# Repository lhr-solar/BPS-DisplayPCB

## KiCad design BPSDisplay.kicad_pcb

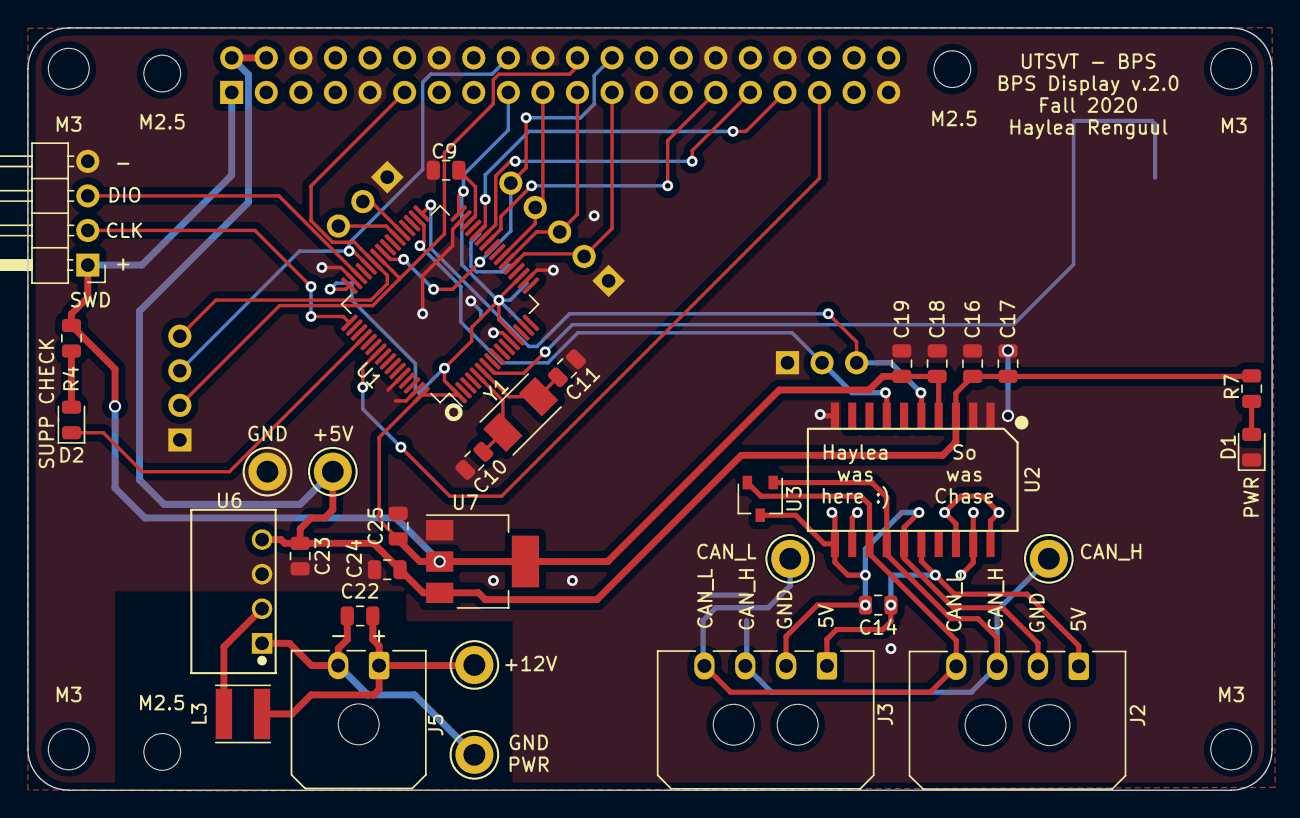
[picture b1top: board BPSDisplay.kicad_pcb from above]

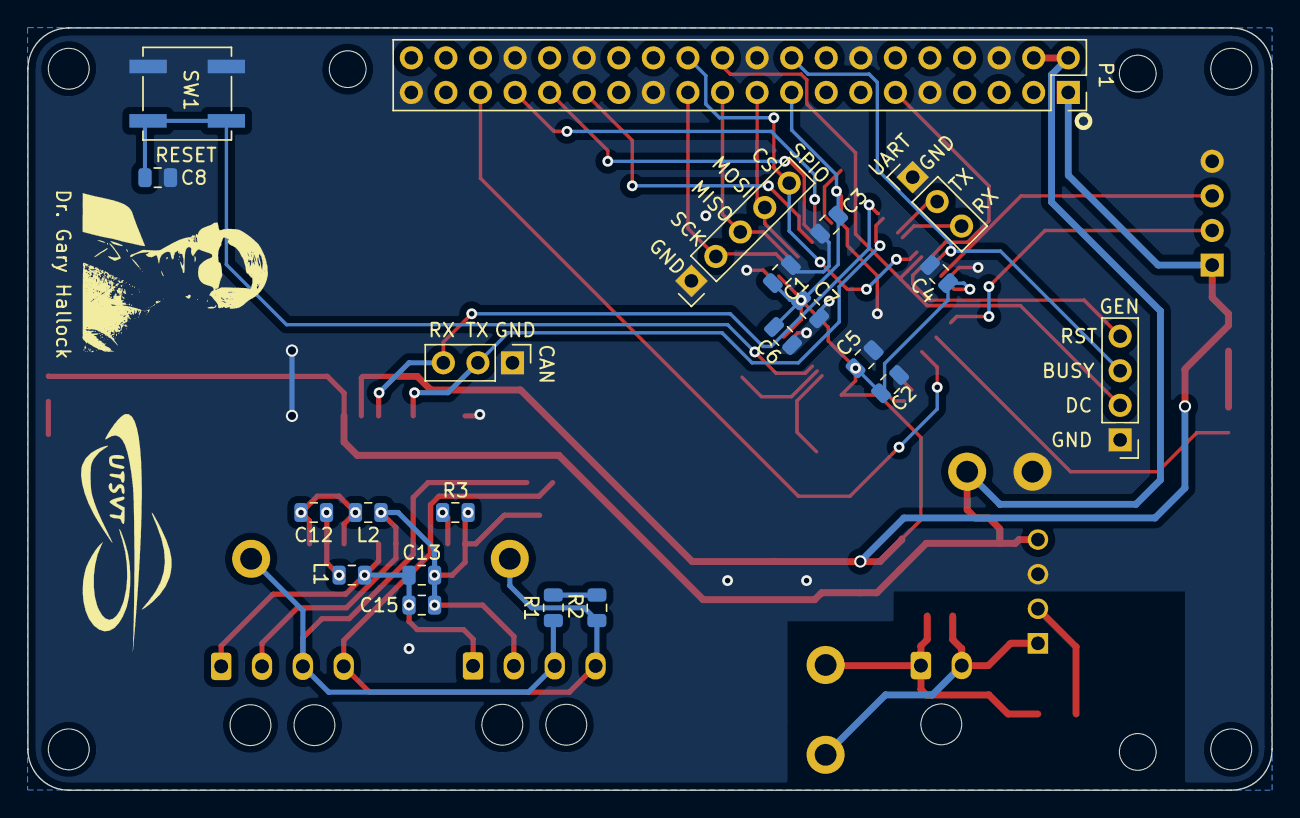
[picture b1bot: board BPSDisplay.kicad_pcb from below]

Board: 2 copper layers, 91.4 x 56.0 mm, 64 parts (24 on the bottom side), 38 nets.

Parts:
C1, C2, C3, C4, C6, C8: 0.1u; C_0805_2012Metric
C5, C22, C23: 4.7u; C_0805_2012Metric
C7: 1u; C_0805_2012Metric
C9: 2.2u; C_0805_2012Metric
C10, C11: 8p; C_0805_2012Metric
C12: 0.22uF; C_0805_2012Metric
C13, C16: 10uF; C_0805_2012Metric
C14, C17, C18: 0.1uF; C_0805_2012Metric
C15, C19: 0.01uF; C_0805_2012Metric
C24, C25: 10u; C_0805_2012Metric
D1, D2: PowerOn; LED_0805_2012Metric
J1: SWD; PinHeader_1x04_P2.54mm_Horizontal
J2, J3: CAN_Out; Molex_Micro-Fit_3.0_43650-0400_1x04_P3.00mm_Horizontal
J5: CarPowerConnector; Molex_Micro-Fit_3.0_43650-0200_1x02_P3.00mm_Horizontal
J6: CAN_LogicAnalyzer; PinHeader_1x03_P2.54mm_Vertical
J7: SPI0_LogicAnalyzer; PinHeader_1x05_P2.54mm_Vertical
J8: GEN_LogicAnalyzer; PinHeader_1x04_P2.54mm_Vertical
J9: USART_LogicAnalyzer; PinHeader_1x03_P2.54mm_Vertical
L1, L2: 2kH; L_0805_2012Metric
L3: 6.8u; L_Taiyo-Yuden_MD-4040
LOGO1: UTSVT; UTSVT_Logo_Symbol
LOGO2: Dr. Hallock; Hallock_Image_Tiny
MK1, MK2, MK4: M2.5; MountingHole_2.7mm_M2.5
MK3, MK5, MK6, MK7: M3; MountingHole_3mm
P1: Conn_02x20_Odd_Even; PinSocket_2x20_P2.54mm_Vertical
R1, R2: 60; R_0805_2012Metric
R3: 0; R_0805_2012Metric
R4: 750; R_0805_2012Metric
R7: 1.5k; R_0805_2012Metric
SW1: Reset; SW_SPST_B3SL-1002P
TP1: CAN_H; TestPoint_Keystone_5005-5009_Compact
TP2: CAN_L; TestPoint_Keystone_5005-5009_Compact
TP3: +3.3V_TP; TestPoint_Keystone_5005-5009_Compact
TP4: +12V_TP; TestPoint_Keystone_5005-5009_Compact
TP5: GNDPWR_TP; TestPoint_Keystone_5005-5009_Compact
TP6: GND_TP; TestPoint_Keystone_5005-5009_Compact
U1: STM32F413RHTx; LQFP-64_10x10mm_P0.5mm
U2: ADM3055E; SOIC-20W_7.5x15.4mm_Pitch1.27mm
U3: CDSOT23-T24CAN; SOT-23W
U6: PDS1-S12-S5; PDSx-S
U7: NCP1117-3.3_SOT223; SOT-223-3_TabPin2
Y1: 8M; Crystal_SMD_TXC_7A-2Pin_5x3.2mm

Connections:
+3V3: C1.1, C2.1, C3.1, C4.1, C5.1, C6.1, C7.1, C18.1, C19.1, C25.1, J1.1, P1.1, P1.17, R4.1, U1.1, U1.13, U1.19, U1.32, U1.48, U1.64, U2.4, U7.2
+5V: C16.1, C17.1, C23.1, C24.1, P1.2, P1.4, R7.1, TP3.1, U2.3, U6.4, U7.3
+12V: C22.1, J5.1, L3.1, TP4.1
/CAN2_RX: J6.3, U1.33, U2.5
/CAN2_TX: J6.2, U1.34, U2.7
/CAN/CAN_H: J2.3, J3.3, R1.2, TP1.1, U2.14, U3.1
/CAN/CAN_L: J2.4, J3.4, R2.2, TP2.1, U2.13, U3.2
/CAN/RSlope: R3.1, U2.12
/GPIO5: P1.29, U1.26
/GPIO6: P1.31, U1.27
/GPIO8(SPI0_CE_N): J7.5, P1.24, U1.41
/GPIO9(SPI0_MISO): J7.3, P1.21, U1.22
/GPIO10(SPI0_MOSI): J7.4, P1.19, U1.23
/GPIO11(SPI0_SCK): J7.2, P1.23, U1.21
/GPIO13: P1.33, U1.28
/GPIO17(GEN0): J8.4, P1.11, U1.43
/GPIO19: P1.35, U1.55
/GPIO24(GEN5): J8.3, P1.18, U1.44
/GPIO25(GEN6): J8.2, P1.22, U1.42
/NRST: C8.1, SW1.1, U1.7
/SWCLK: J1.2, U1.49
/SWDIO: J1.3, U1.46
/USART6_RX: J9.3, U1.38
/USART6_TX: J9.2, U1.37
GND: C1.2, C2.2, C3.2, C4.2, C5.2, C6.2, C7.2, C8.2, C9.2, C10.2, C11.2, C16.2, C17.2, C18.2, C19.2, C23.2, C24.2, C25.2, D1.1, J1.4, J6.1, J7.1, J8.1, J9.1, P1.6, P1.9, P1.14, P1.20, P1.25, P1.30, P1.34, P1.39, SW1.2, TP6.1, U1.12, U1.18, U1.31, U1.47, U1.60, U1.63, U2.1, U2.2, U2.10, U6.3, U7.1
GNDPWR: C22.2, J5.2, TP5.1, U6.1
unnamed: C9.1, U1.30
unnamed: C10.1, U1.5, Y1.1
unnamed: C11.1, U1.6, Y1.2
unnamed: C12.1, L1.2, U2.19
unnamed: C12.2, L2.2, U2.18, U2.20
unnamed: C13.1, C14.1, C15.1, J2.1, J3.1, L1.1, U2.16
unnamed: C13.2, C14.2, C15.2, J2.2, J3.2, L2.1, R3.2, U2.11, U2.15, U3.3
unnamed: D1.2, R7.2
unnamed: D2.1, U1.52
unnamed: D2.2, R4.2
unnamed: L3.2, U6.2
unnamed: R1.1, R2.1

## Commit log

2020-08-02 Set up for own repository
2020-09-12 Deleted hierarchical sheets
    Deleted the hierarchical sheets that were at the bottom left of the schematic (CAN, isoSPI, and Power Distribution) and deleted the connections to them (CAN2_TX, CAN2_RX, SPI3_SCK, SPI3_MISO, SPI3_MO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
2020-09-12 Deleted the isoSPI sheet and connections
    On the schematic, I deleted the isoSPI sheet and its connections to the STM (replaced them with no connection flags). I updated the PCB from that so it now has all the components that need to be arra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
2020-09-13 Updated CAN sheet
    Fixed the CAN interface schematic so it follows the recommended layout. The footprint for the ADM is from the BPS-Master-rescue.lib file so I'm uploading that as well.
2020-09-19 Reattached Lib to project for correct symbol model
2020-09-19 Confimred Schematic and generated Netlist
2020-09-19 Rearranging PCB layout
    Power distribution circuit is laid out, CAN interface is done using the recommended PCB layout, and all the mounting holes and connectors are in the same places as they were in the old board.
2020-09-19 Added traces
    We added some preliminary traces to the PCB. There are a few pins that are still unconnected.
2020-09-26 Completed Traces and resized to correct dim.
2020-09-26 Added Labels
2020-10-03 Adds QuAC
2020-10-03 Edits to PCB layout
    Rounded out corners of the board, added pin labels to connectors, rearranged trace that was too close to U1
2020-10-03 Making left edge cut straight
2020-10-03 Editing PCB layout
    Moved mounting holes into the correct order/spots, moved U6 closer to the left edge of the board (since it's a taller component), removed the sharp angle near C17
2020-10-03 Removed traces under Y1
    Also aligned J5 with U6
2020-10-10 Split Logic Analyzer
    & added second CAN connector
2020-10-10 Added footprints to connectors
    Made all connector footprints horizontal too
2020-10-10 New PCB layout
    Split logic analyzer into different connector pins, added labels, moved all connectors to south side of the board
2020-10-10 Added circle to indicate pin 1 of U2
2020-10-17 Updated footprints, re-routed traces
    Changed logical analyzer footprints to vertical, changed 2x20 connector footprint back to the original footprint, changed CAN headers to vertical footprints.
    Grouped components better so logic analyzer pins are closer to their corresponding pins on the microcontroller. Re-did traces accordingly.
2020-10-17 Updated footprints, re-routed traces
2020-10-17 Fixed traces
    Got rid of traces with right angles, made labels on CAN headers vertical, made traces neater, added logo and picture of Dr. Hallock on back
2020-10-24 Aligning components, editing text
    Aligned connectors on the south end to the edge of the board, edited text for title of the board, rotated JP1 90 degrees clockwise, and removed the trace appendage on C5.
2020-11-07 Fixed labels
2020-11-07 Moved traces to avoid shorts
2020-12-18 Adds LED for supplementals, deletes unncessary files, and links all symbols to the submodule
2020-12-19 Redo most of the layout to fix issues.
2020-12-19 Adds another mounting hole, moves PWR LED, and adds labels to test points
2021-01-23 3-D Models
    Adds 3-D models for switch, crystal, connectors, and chips. Adds FreeCAD file for the PCB.
2021-10-31 Reorganized the board for practice using KiCAD
2021-11-13 reorganized PCB layout
